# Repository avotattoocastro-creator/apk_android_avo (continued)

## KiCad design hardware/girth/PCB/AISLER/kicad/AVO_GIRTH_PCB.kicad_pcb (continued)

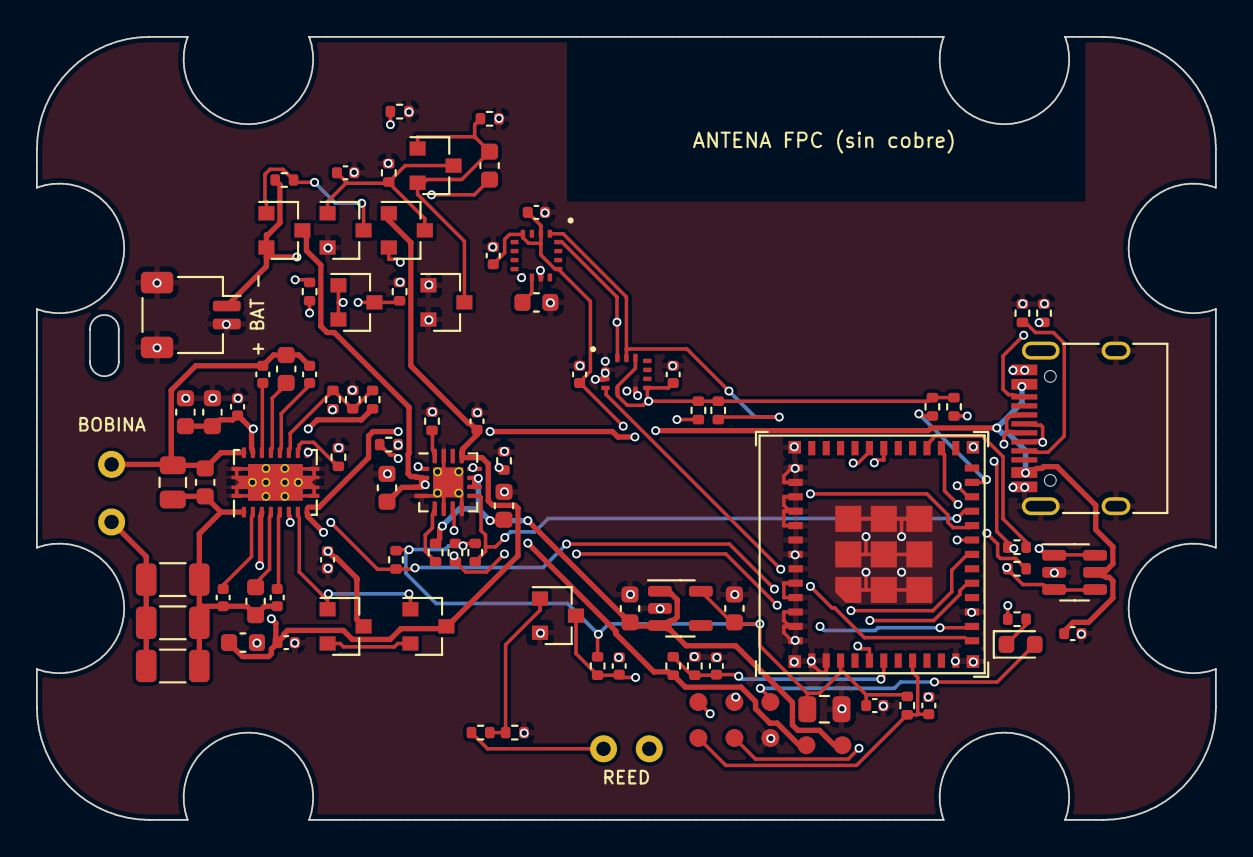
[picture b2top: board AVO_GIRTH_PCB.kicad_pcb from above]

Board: 4 copper layers, 65.5 x 43.5 mm, 98 parts (0 on the bottom side), 55 nets.

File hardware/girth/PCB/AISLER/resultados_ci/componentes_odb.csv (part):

ref,capa,x_mm,y_mm,giro,no_pop,montaje,Value,MPN,Manufacturer,LCSC,paquete
C1,COMP_+_TOP,74.8,-108.4,0.0,False,smt,100n C0G 50V,GRM31C5C1H104JA01L,Murata Electronics,C97946,AVO_C_1206_3216Metric
C2,COMP_+_TOP,74.8,-110.8,0.0,False,smt,100n C0G 50V,GRM31C5C1H104JA01L,Murata Electronics,C97946,AVO_C_1206_3216Metric
C3,COMP_+_TOP,74.8,-113.2,0.0,False,smt,47n C0G 50V,GRM31M5C1H473JA01L,Murata Electronics,C21812,AVO_C_1206_3216Metric
C4,COMP_+_TOP,74.8,-103.0,270.0,False,smt,2n2 C0G 50V,0805CG222J500NT,FH (Guangdong Fenghua Advanced Tech),C51795,AVO_C_0805_2012Metric
C5,COMP_+_TOP,76.6,-103.0,270.0,True,smt,1n C0G 50V,1n C0G 50V,,C1636,AVO_C_0603_1608Metric
C6,COMP_+_TOP,77.6,-109.4,90.0,False,smt,10n 50V,CL05B103KB5NNNC,Samsung Electro-Mechanics,C15195,AVO_C_0402_1005Metric
C7,COMP_+_TOP,79.4,-109.6,90.0,False,smt,470n 25V,CL10B474KA8NNNC,Samsung Electro-Mechanics,C1623,AVO_C_0603_1608Metric
C8,COMP_+_TOP,80.6,-109.4,90.0,False,smt,22n 50V,0402B223K500NT,FH (Guangdong Fenghua Advanced Tech),C1532,AVO_C_0402_1005Metric
C9,COMP_+_TOP,79.8,-97.0,270.0,False,smt,10n 50V,CL05B103KB5NNNC,Samsung Electro-Mechanics,C15195,AVO_C_0402_1005Metric
C10,COMP_+_TOP,81.1,-96.7,270.0,False,smt,470n 25V,CL10B474KA8NNNC,Samsung Electro-Mechanics,C1623,AVO_C_0603_1608Metric
C11,COMP_+_TOP,82.4,-97.0,270.0,False,smt,22n 50V,0402B223K500NT,FH (Guangdong Fenghua Advanced Tech),C1532,AVO_C_0402_1005Metric
C12,COMP_+_TOP,77.0,-99.1,270.0,False,smt,10u 25V,CL10A106MA8NRNC,Samsung Electro-Mechanics,C96446,AVO_C_0603_1608Metric
C13,COMP_+_TOP,75.5,-99.1,270.0,False,smt,10u 25V,CL10A106MA8NRNC,Samsung Electro-Mechanics,C96446,AVO_C_0603_1608Metric
C14,COMP_+_TOP,78.4,-98.8,270.0,False,smt,100n,CL05B104KO5NNNC,Samsung Electro-Mechanics,C1525,AVO_C_0402_1005Metric
C15,COMP_+_TOP,78.7,-111.9,0.0,False,smt,10u 25V,CL10A106MA8NRNC,Samsung Electro-Mechanics,C96446,AVO_C_0603_1608Metric
C16,COMP_+_TOP,81.1,-111.9,0.0,False,smt,100n,CL05B104KO5NNNC,Samsung Electro-Mechanics,C1525,AVO_C_0402_1005Metric
C17,COMP_+_TOP,83.4,-107.3,90.0,False,smt,1u,CL05A105KA5NQNC,Samsung Electro-Mechanics,C52923,AVO_C_0402_1005Metric
C18,COMP_+_TOP,91.7,-99.6,270.0,False,smt,1u,CL05A105KA5NQNC,Samsung Electro-Mechanics,C52923,AVO_C_0402_1005Metric
C19,COMP_+_TOP,93.2,-104.3,270.0,False,smt,10u 25V,CL10A106MA8NRNC,Samsung Electro-Mechanics,C96446,AVO_C_0603_1608Metric
C20,COMP_+_TOP,86.7,-103.3,270.0,False,smt,10u 25V,CL10A106MA8NRNC,Samsung Electro-Mechanics,C96446,AVO_C_0603_1608Metric
C21,COMP_+_TOP,100.2,-110.0,270.0,False,smt,10u 25V,CL10A106MA8NRNC,Samsung Electro-Mechanics,C96446,AVO_C_0603_1608Metric
C22,COMP_+_TOP,106.0,-110.0,270.0,False,smt,10u 25V,CL10A106MA8NRNC,Samsung Electro-Mechanics,C96446,AVO_C_0603_1608Metric
C23,COMP_+_TOP,111.0,-115.6,0.0,False,smt,22u 10V,CL21A226MAQNNNE,Samsung Electro-Mechanics,C45783,AVO_C_0805_2012Metric
C24,COMP_+_TOP,113.8,-115.4,0.0,False,smt,100n,CL05B104KO5NNNC,Samsung Electro-Mechanics,C1525,AVO_C_0402_1005Metric
C25,COMP_+_TOP,116.8,-115.4,270.0,False,smt,1u,CL05A105KA5NQNC,Samsung Electro-Mechanics,C52923,AVO_C_0402_1005Metric
C26,COMP_+_TOP,124.8,-111.4,0.0,False,smt,1u,CL05A105KA5NQNC,Samsung Electro-Mechanics,C52923,AVO_C_0402_1005Metric
C27,COMP_+_TOP,97.4,-97.0,270.0,False,smt,100n,CL05B104KO5NNNC,Samsung Electro-Mechanics,C1525,AVO_C_0402_1005Metric
C28,COMP_+_TOP,102.6,-97.0,270.0,False,smt,100n,CL05B104KO5NNNC,Samsung Electro-Mechanics,C1525,AVO_C_0402_1005Metric
C29,COMP_+_TOP,92.6,-90.4,270.0,False,smt,1u,CL05A105KA5NQNC,Samsung Electro-Mechanics,C52923,AVO_C_0402_1005Metric
C30,COMP_+_TOP,95.0,-93.0,0.0,False,smt,10u 6V3,CL10A106KP8NNNC,Samsung Electro-Mechanics,C19702,AVO_C_0603_1608Metric
C31,COMP_+_TOP,95.0,-88.0,0.0,False,smt,100n,CL05B104KO5NNNC,Samsung Electro-Mechanics,C1525,AVO_C_0402_1005Metric
C33,COMP_+_TOP,99.6,-113.2,270.0,False,smt,10n 50V,CL05B103KB5NNNC,Samsung Electro-Mechanics,C15195,AVO_C_0402_1005Metric
C34,COMP_+_TOP,105.0,-113.2,270.0,False,smt,100n,CL05B104KO5NNNC,Samsung Electro-Mechanics,C1525,AVO_C_0402_1005Metric
C40,COMP_+_TOP,92.4,-85.4,270.0,False,smt,2u2,CL10A225KO8NNNC,Samsung Electro-Mechanics,C23630,AVO_C_0603_1608Metric
C41,COMP_+_TOP,84.4,-85.8,0.0,False,smt,220n,CL05B224KO5NNNC,Samsung Electro-Mechanics,C16772,AVO_C_0402_1005Metric
D1,COMP_+_TOP,121.9,-112.0,0.0,False,smt,LED rojo,KT-0603R,Hubei KENTO Elec,C2286,AVO_LED_0603_1608Metric
D10,COMP_+_TOP,87.8,-89.0,0.0,False,smt,BAV70,BAV70,"Jiangsu Changjing Electronics Technology Co., Ltd.",C68978,AVO_SOT-23
D11,COMP_+_TOP,89.4,-85.4,0.0,False,smt,BAV70,BAV70,"Jiangsu Changjing Electronics Technology Co., Ltd.",C68978,AVO_SOT-23
D12,COMP_+_TOP,85.0,-93.0,0.0,False,smt,BAV70,BAV70,"Jiangsu Changjing Electronics Technology Co., Ltd.",C68978,AVO_SOT-23
D13,COMP_+_TOP,90.0,-93.0,0.0,False,smt,BAV70,BAV70,"Jiangsu Changjing Electronics Technology Co., Ltd.",C68978,AVO_SOT-23
J1,COMP_+_TOP,126.15,-100.0,270.0,False,smt,USB-C 16P,TYPE-C-31-M-12,Korean Hroparts Elec,C165948,AVO_USB_C_Receptacle_HRO_TYPE-C-31-M-12
J2,COMP_+_TOP,75.8,-93.7,90.0,False,smt,BATERÍA 1S,SM02B-SRSS-TB(LF)(SN),JST,C160402,AVO_JST_SH_SM02B-SRSS-TB_1x02-1MP_P1.00mm_Horizontal
L1,COMP_+_TOP,71.4,-105.2,0.0,True,thmt,BOBINA Qi (1),BOBINA Qi (1),,,AVO_WirePad_D1.5_Drill0.8
L2,COMP_+_TOP,71.4,-102.0,0.0,True,thmt,BOBINA Qi (2),BOBINA Qi (2),,,AVO_WirePad_D1.5_Drill0.8
Q1,COMP_+_TOP,84.4,-111.0,0.0,False,smt,AO3401A,AO3401A,Alpha & Omega Semicon,C15127,AVO_SOT-23
Q2,COMP_+_TOP,89.0,-111.0,0.0,False,smt,AO3401A,AO3401A,Alpha & Omega Semicon,C15127,AVO_SOT-23
Q10,COMP_+_TOP,81.0,-89.0,0.0,False,smt,AO3401A,AO3401A,Alpha & Omega Semicon,C15127,AVO_SOT-23
Q11,COMP_+_TOP,84.4,-89.0,0.0,False,smt,AO3400A,AO3400A,Alpha & Omega Semicon,C20917,AVO_SOT-23
Q16,COMP_+_TOP,96.2,-110.4,0.0,False,smt,2N7002,2N7002,"Jiangsu Changjing Electronics Technology Co., Ltd.",C8545,AVO_SOT-23
R1,COMP_+_TOP,83.7,-98.4,270.0,False,smt,330R,0402WGF3300TCE,UNI-ROYAL(Uniroyal Elec),C25104,AVO_R_0402_1005Metric
R2,COMP_+_TOP,84.8,-98.4,270.0,False,smt,200R,0402WGF2000TCE,UNI-ROYAL(Uniroyal Elec),C25087,AVO_R_0402_1005Metric
R3,COMP_+_TOP,85.9,-98.4,270.0,False,smt,20k,0402WGF2002TCE,UNI-ROYAL(Uniroyal Elec),C25765,AVO_R_0402_1005Metric
R4,COMP_+_TOP,87.2,-107.3,270.0,False,smt,100k,0402WGF1003TCE,UNI-ROYAL(Uniroyal Elec),C25741,AVO_R_0402_1005Metric
R6,COMP_+_TOP,89.2,-99.6,270.0,False,smt,3k3,0402WGF3301TCE,UNI-ROYAL(Uniroyal Elec),C25890,AVO_R_0402_1005Metric
R7,COMP_+_TOP,93.2,-101.8,270.0,False,smt,3k3,0402WGF3301TCE,UNI-ROYAL(Uniroyal Elec),C25890,AVO_R_0402_1005Metric
R8,COMP_+_TOP,89.4,-106.9,270.0,False,smt,100k,0402WGF1003TCE,UNI-ROYAL(Uniroyal Elec),C25741,AVO_R_0402_1005Metric
R9,COMP_+_TOP,90.5,-106.9,270.0,False,smt,100k,0402WGF1003TCE,UNI-ROYAL(Uniroyal Elec),C25741,AVO_R_0402_1005Metric
R10,COMP_+_TOP,91.6,-106.9,270.0,False,smt,100k,0402WGF1003TCE,UNI-ROYAL(Uniroyal Elec),C25741,AVO_R_0402_1005Metric
R11,COMP_+_TOP,115.6,-115.4,270.0,False,smt,10k,0402WGF1002TCE,UNI-ROYAL(Uniroyal Elec),C25744,AVO_R_0402_1005Metric
R12,COMP_+_TOP,117.0,-98.8,270.0,False,smt,10k,0402WGF1002TCE,UNI-ROYAL(Uniroyal Elec),C25744,AVO_R_0402_1005Metric
R13,COMP_+_TOP,118.2,-98.8,270.0,False,smt,10k,0402WGF1002TCE,UNI-ROYAL(Uniroyal Elec),C25744,AVO_R_0402_1005Metric
R15,COMP_+_TOP,121.7,-110.6,0.0,False,smt,1k,0402WGF1001TCE,UNI-ROYAL(Uniroyal Elec),C11702,AVO_R_0402_1005Metric
R16,COMP_+_TOP,122.0,-93.6,270.0,False,smt,5k1,0402WGF5101TCE,UNI-ROYAL(Uniroyal Elec),C25905,AVO_R_0402_1005Metric
R17,COMP_+_TOP,123.2,-93.6,270.0,False,smt,5k1,0402WGF5101TCE,UNI-ROYAL(Uniroyal Elec),C25905,AVO_R_0402_1005Metric
R18,COMP_+_TOP,121.7,-106.6,0.0,False,smt,22R,0402WGF220JTCE,UNI-ROYAL(Uniroyal Elec),C25092,AVO_R_0402_1005Metric
R19,COMP_+_TOP,121.7,-107.8,0.0,False,smt,22R,0402WGF220JTCE,UNI-ROYAL(Uniroyal Elec),C25092,AVO_R_0402_1005Metric
R20,COMP_+_TOP,104.0,-99.0,270.0,False,smt,4k7,0402WGF4701TCE,UNI-ROYAL(Uniroyal Elec),C25900,AVO_R_0402_1005Metric
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
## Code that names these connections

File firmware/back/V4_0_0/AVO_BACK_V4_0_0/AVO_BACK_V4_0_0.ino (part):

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}

static bool sd_start() {
  pinMode(PIN_SD_PWR_N, OUTPUT);
  digitalWrite(PIN_SD_PWR_N, LOW);           // card powered
  delay(20);
  if (!SD_MMC.setPins(PIN_SD_CLK, PIN_SD_CMD, PIN_SD_D0, PIN_SD_D1, PIN_SD_D2, PIN_SD_D3)) return false;
  if (!SD_MMC.begin("/sdcard", false, false, SDMMC_FREQ_DEFAULT, 2)) {
    digitalWrite(PIN_SD_PWR_N, HIGH);
    return false;
  }
  uint32_t n = prefs.getUInt("logn", 0) + 1;
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static void sd_stop() {
  s_sd_ok = false;
  SD_MMC.end();
  pinMode(PIN_SD_PWR_N, OUTPUT);
  digitalWrite(PIN_SD_PWR_N, HIGH);          // card off
}

static void sd_task(void*) {
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static BackCore* core = nullptr;

// ------------------------------------------------------------------ helpers
static bool usb_power() { return digitalRead(PIN_CHG_PG) == LOW; }     // workshop USB-C present
static bool charging() { return digitalRead(PIN_CHG_STAT) == LOW; }
static void led(bool on) { digitalWrite(PIN_LED, on ? LOW : HIGH); }

static uint16_t read_battery_mv() {
  uint32_t acc = 0;
  for (int i = 0; i < 16; i++) acc += analogReadMilliVolts(PIN_BAT_ADC);
  return battery_mv_from_adc(acc / 16);
}

static void zed_lines_safe() {               // unpowered ZED must not be fed through its RX lines
  pinMode(PIN_S3_TX1, OUTPUT); digitalWrite(PIN_S3_TX1, LOW);
  pinMode(PIN_S3_TX2, OUTPUT); digitalWrite(PIN_S3_TX2, LOW);
  pinMode(PIN_ZED_TX1, INPUT); pinMode(PIN_ZED_TX2, INPUT);
  pinMode(PIN_ZED_RST, INPUT);
}

static void zed_power_on() {
  gpio_hold_dis((gpio_num_t)PIN_ZED_EN);
  pinMode(PIN_ZED_EN, OUTPUT);
  digitalWrite(PIN_ZED_EN, HIGH);            // RT9080 on (its soft start; the ESP32 3V3 is a separate regulator)
  delay(50);
  ZED.setRxBufferSize(8192);
  ZED.setTxBufferSize(4096);
  ZED.begin(38400, SERIAL_8N1, PIN_ZED_TX2, PIN_S3_TX2);   // RX, TX
  ZED.setRxTimeout(1);
  s_zed_on = true;
  pinMode(PIN_ZED_PPS, INPUT);
  attachInterrupt(digitalPinToInterrupt(PIN_ZED_PPS), on_pps, RISING);
  Serial.println("[AVO ESPALDA V4] ZED alimentado (RT9080, EN = GPIO10)");
}

static void zed_power_off() {
  if (s_zed_on) { detachInterrupt(digitalPinToInterrupt(PIN_ZED_PPS)); ZED.end(); s_zed_on = false; }
  s_zed_pending = false;
  zed_lines_safe();
  pinMode(PIN_ZED_EN, OUTPUT);
  digitalWrite(PIN_ZED_EN, LOW);             // 0 V on the receiver and the active antenna
}

static void radio_on() {
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  radio_off();
  if (s_sd_ok) { delay(300); sd_stop(); }
  zed_power_off();
  gpio_hold_en((gpio_num_t)PIN_ZED_EN);
  gpio_hold_en((gpio_num_t)PIN_S3_TX1);
  gpio_hold_en((gpio_num_t)PIN_S3_TX2);
  pinMode(PIN_SD_PWR_N, OUTPUT); digitalWrite(PIN_SD_PWR_N, HIGH); gpio_hold_en((gpio_num_t)PIN_SD_PWR_N);
  led(false); gpio_hold_en((gpio_num_t)PIN_LED);
#if SOC_GPIO_SUPPORT_HOLD_IO_IN_DSLP && !SOC_GPIO_SUPPORT_HOLD_SINGLE_IO_IN_DSLP
  gpio_deep_sleep_hold_en();
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#if SOC_GPIO_SUPPORT_HOLD_IO_IN_DSLP && !SOC_GPIO_SUPPORT_HOLD_SINGLE_IO_IN_DSLP
  gpio_deep_sleep_hold_dis();
#endif
  for (int p : {PIN_ZED_EN, PIN_S3_TX1, PIN_S3_TX2, PIN_SD_PWR_N, PIN_LED}) gpio_hold_dis((gpio_num_t)p);
  zed_power_off();                           // ZED at 0 V until the 3V3 rail and the ESP32 are up
  pinMode(PIN_SD_PWR_N, OUTPUT); digitalWrite(PIN_SD_PWR_N, HIGH);
  pinMode(PIN_LED, OUTPUT); led(true);
  pinMode(PIN_CHG_PG, INPUT); pinMode(PIN_CHG_STAT, INPUT);
  pinMode(PIN_SD_CD, INPUT);
  analogSetPinAttenuation(PIN_BAT_ADC, ADC_11db);
  setCpuFrequencyMhz(CPU_MHZ);
  delay(300);
  // REV B: having power means the capsule is on the vest support (or on the workshop USB): everything starts.
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
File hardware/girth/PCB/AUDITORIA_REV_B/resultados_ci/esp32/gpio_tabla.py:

"""Tabla GPIO firmware ↔ esquema/placa (fase 5). Fuentes independientes:
 - firmware: firmware/girth/V0_3_0_C3/AVO_GIRTH_V0_3_0/girth_board.h (PIN_*)
 - módulo: símbolo oficial de Espressif (ESP32-C3-MINI-1, número de pin → GPIO)
 - placa: red de cada pad de U4 en la placa entregada (out/C3/KiCad/AVO_GIRTH_PCB.kicad_pcb)
Uso: python3 gpio_tabla.py [ruta_simbolo_espressif]  → gpio_tabla.md + gpio_tabla.json"""
import json
import os
import re
import sys

H = os.path.dirname(os.path.abspath(__file__))
ROOT = os.path.join(H, "..", "..", "..", "..", "..")
SYM = sys.argv[1] if len(sys.argv) > 1 else os.path.join(H, "ESP32-C3-MINI-1_simbolo_espressif.kicad_sym.txt")
board_h = open(os.path.join(ROOT, "firmware/girth/V0_3_0_C3/AVO_GIRTH_V0_3_0/girth_board.h")).read()
fw = {name: int(v) for name, v in re.findall(r"static const int (PIN_\w+)\s*=\s*(\d+);", board_h)}
# símbolo: pines del ESP32-C3-MINI-1 (el -1U usa el mismo)
s = open(SYM).read()
i = s.find('(symbol "ESP32-C3-MINI-1"'); j = s.find('\n\t(symbol "', i + 10)
blk = s[i:j]
pin_gpio = {}
for name, num in re.findall(r'\(pin \w+ \w+.*?\(name "([^"]*)".*?\(number "([^"]*)"', blk, re.S):
    m = re.match(r"GPIO(\d+)", name)
    if m:
        pin_gpio[num] = int(m.group(1))
gpio_pin = {g: p for p, g in pin_gpio.items()}
# placa: red de cada pad de U4
pcb = open(os.path.join(ROOT, "hardware/girth/PCB/out/C3/KiCad/AVO_GIRTH_PCB.kicad_pcb")).read()
u4 = [b for b in pcb.split("\n\t(footprint ")[1:] if re.search(r'"Reference" "U4"', b)][0]
pad_net = {}
for m in re.finditer(r'\(pad "(\d+)".*?\(net \d+ "([^"]*)"\)', u4, re.S):
    pad_net.setdefault(m.group(1), m.group(2))
EXPECT = {"PIN_IMU_INT": "IMU_INT", "PIN_REED": "REED", "PIN_SCL": "I2C_SCL", "PIN_BAT_ADC": "BAT_ADC",
          "PIN_CHG_PG": "CHG_PG", "PIN_PWR_HOLD": "PWR_HOLD", "PIN_SDA": "I2C_SDA", "PIN_CHG_STAT": "CHG_STAT",
          "PIN_LED": "LED", "PIN_BOOT": "BOOT", "PIN_QI_CHG": "QI_CHG"}
rows, bad = [], 0
for name, g in sorted(fw.items(), key=lambda kv: kv[1]):
    pin = gpio_pin.get(g)
    net = pad_net.get(pin)
    ok = net == EXPECT.get(name)
    bad += not ok
    rows.append(dict(firmware=name, gpio=g, pin_modulo=pin, red_placa=net, esperada=EXPECT.get(name), ok=ok))
for g, fixed in ((18, "USB_DM"), (19, "USB_DP"), (20, "U0RX"), (21, "U0TX")):
    pin = gpio_pin.get(g); net = pad_net.get(pin); ok = net == fixed; bad += not ok
    rows.append(dict(firmware="(núcleo: USB / UART0)", gpio=g, pin_modulo=pin, red_placa=net, esperada=fixed, ok=ok))
used = {r["gpio"] for r in rows}
free = sorted(set(pin_gpio.values()) - used)
L = ["| Nombre en el firmware | GPIO | Pin del módulo | Red en la placa | Esperada | Coincide |", "|---|---|---|---|---|---|"]
for r in rows:
    L.append("| %s | %d | %s | %s | %s | %s |" % (r["firmware"], r["gpio"], r["pin_modulo"], r["red_placa"], r["esperada"],
                                              "sí" if r["ok"] else "**NO**"))
L.append("")
L.append("GPIO del módulo sin usar: %s · discrepancias: %d" % (free or "ninguno", bad))
open(os.path.join(H, "gpio_tabla.md"), "w").write("\n".join(L) + "\n")
json.dump(dict(filas=rows, libres=free, discrepancias=bad), open(os.path.join(H, "gpio_tabla.json"), "w"), indent=1)
print("\n".join(L))
sys.exit(1 if bad else 0)
